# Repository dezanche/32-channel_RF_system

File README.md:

The 32-Channel RF Signal Amplifier and Attenuator System is a modular amplifier and attenuation system designed to provide 2nd stage amplification in close proximity to an MRI scanner. With proper choice of components it can readily be adapted to a wide range of Larmor frequencies and applications. Each channel’s amplifier and attenuator circuitry is housed on a separate daughterboard for flexibility and easy servicing.

These Daughterboards stand perpendicular to a larger Motherboard which contains all the common circuitry such as power distribution and protection circuitry, as well as the interface for attenuation control.

Additional information is provided in [this YouTube video](https://www.youtube.com/watch?v=jpFOpedchC8).

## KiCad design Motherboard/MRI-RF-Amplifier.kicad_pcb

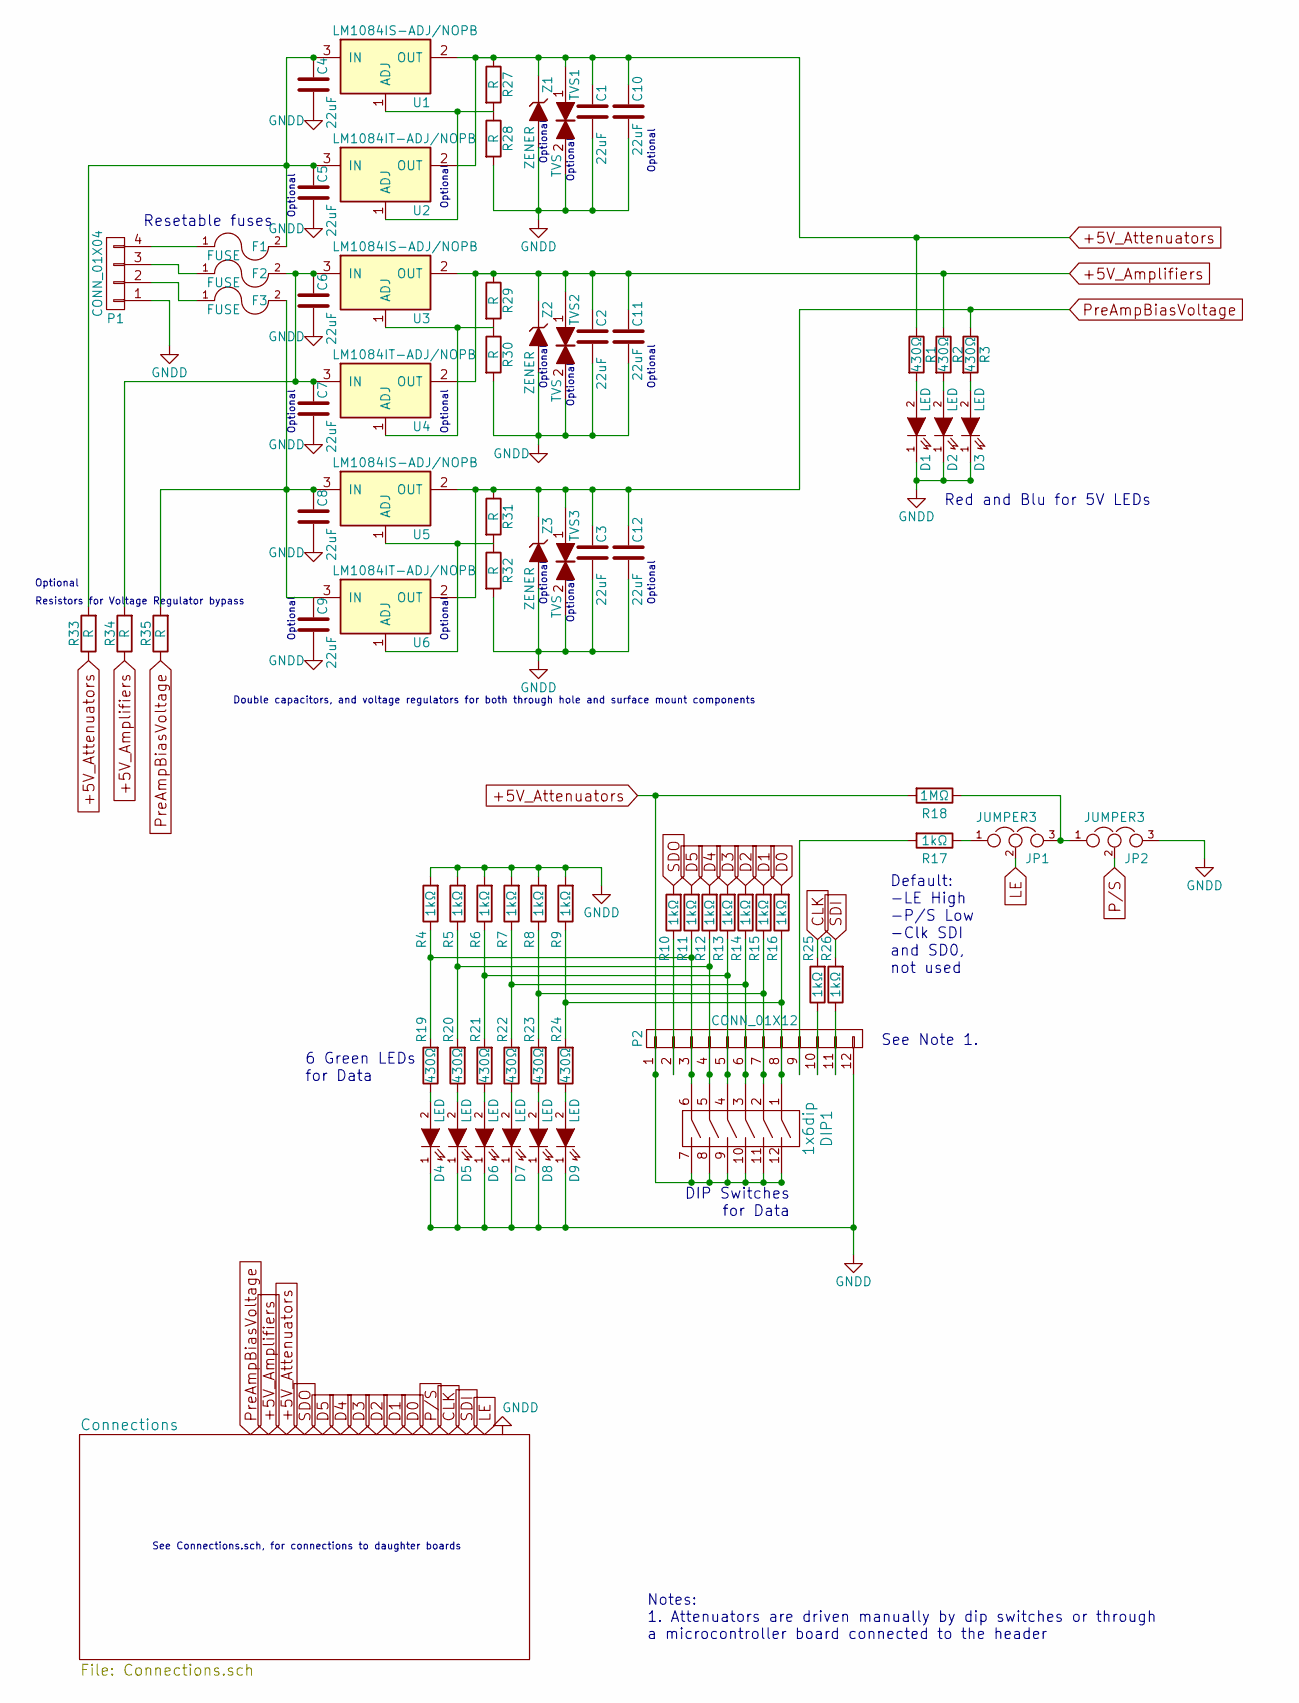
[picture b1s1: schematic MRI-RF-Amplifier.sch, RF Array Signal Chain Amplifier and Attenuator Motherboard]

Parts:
C1, C2, C3, C4, C6, C8: 22uF; C_1206_HandSoldering
C5, C7, C9, C10, C11, C12: 22uF; CP_Radial_D5.0mm_P2.00mm
D1, D2, D3, D4, D5, D6, D7, D8, D9: LED; LED_1206
DIP1: 1x6dip; DIP_SPSTx6
F1, F2, F3: FUSE; C_1210_HandSoldering
JP1, JP2: JUMPER3; Molex_KK-6410-03_03x2.54mm_Straight
P1: CONN_01X04; OSTTC0421162
P2: CONN_01X12; Pin_Header_Straight_1x12_Pitch2.54mm
R1, R2, R3, R19, R20, R21, R22, R23, R24: 430Ω; R_1206_HandSoldering
R4, R5, R6, R7, R8, R9, R10, R11, R12, R13, R14, R15, R16, R17, R25, R26: 1kΩ; R_1206_HandSoldering
R18: 1MΩ; R_1206_HandSoldering
R27, R28, R29, R30, R31, R32, R33, R34, R35: R; R_1206_HandSoldering
TVS1, TVS2, TVS3: TVS; D_SOD-323_HandSoldering
U1, U3, U5: LM1084IS-ADJ/NOPB; TO-263-3_TabPin2
U2, U4, U6: LM1084IT-ADJ/NOPB; TO-220_Horizontal
Z1, Z2, Z3: ZENER; D_SMB_Handsoldering

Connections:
+5V_Amplifiers: C2.1, C11.1, R2.1, R29.1, R34.1, TVS2.1, U3.2 (OUT), U4.2 (OUT), Z2.1 (K); also elsewhere on the board
+5V_Attenuators: C1.1, C10.1, DIP1.7, DIP1.8, DIP1.9, DIP1.10, DIP1.11, DIP1.12, P2.1, R1.1, R18.2, R27.1, R33.1, TVS1.1, U1.2 (OUT), U2.2 (OUT), Z1.1 (K); also elsewhere on the board
CLK: R25.2; also elsewhere on the board
D0: R16.2; also elsewhere on the board
D1: R15.2; also elsewhere on the board
D2: R14.2; also elsewhere on the board
D3: R13.2; also elsewhere on the board
D4: R12.2; also elsewhere on the board
D5: R11.2; also elsewhere on the board
GNDD: C1.2, C2.2, C3.2, C4.2, C5.2, C6.2, C7.2, C8.2, C9.2, C10.2, C11.2, C12.2, D1.1 (K), D2.1 (K), D3.1 (K), D4.1 (K), D5.1 (K), D6.1 (K), D7.1 (K), D8.1 (K), D9.1 (K), JP2.3, P1.1, P2.12, R4.2, R5.2, R6.2, R7.2, R8.2, R9.2, R28.2, R30.2, R32.2, TVS1.2, TVS2.2, TVS3.2, Z1.2 (A), Z2.2 (A), Z3.2 (A); also elsewhere on the board
LE: JP1.2; also elsewhere on the board
unnamed: C4.1, C5.1, F1.2, R33.2, U1.3 (IN), U2.3 (IN)
unnamed: C6.1, C7.1, F2.2, R34.2, U3.3 (IN), U4.3 (IN)
unnamed: C8.1, C9.1, F3.2, R35.2, U5.3 (IN), U6.3 (IN)
unnamed: D1.2 (A), R1.2
unnamed: D2.2 (A), R2.2
unnamed: D3.2 (A), R3.2
unnamed: D4.2 (A), R19.1
unnamed: D5.2 (A), R20.1
unnamed: D6.2 (A), R21.1
unnamed: D7.2 (A), R22.1
unnamed: D8.2 (A), R23.1
unnamed: D9.2 (A), R24.1
unnamed: DIP1.1, P2.8, R9.1, R16.1, R24.2
unnamed: DIP1.2, P2.7, R8.1, R15.1, R23.2
unnamed: DIP1.3, P2.6, R7.1, R14.1, R22.2
unnamed: DIP1.4, P2.5, R6.1, R13.1, R21.2
unnamed: DIP1.5, P2.4, R5.1, R12.1, R20.2
unnamed: DIP1.6, P2.3, R4.1, R11.1, R19.2
unnamed: F1.1, P1.4
unnamed: F2.1, P1.3
unnamed: F3.1, P1.2
unnamed: JP1.1, R17.1
unnamed: JP1.3, JP2.1, R18.1
unnamed: P2.2, R10.1
unnamed: P2.9, R17.2
unnamed: P2.10, R25.1
unnamed: P2.11, R26.1
unnamed: R27.2, R28.1, U1.1 (ADJ), U2.1 (ADJ)
unnamed: R29.2, R30.1, U3.1 (ADJ), U4.1 (ADJ)
unnamed: R31.2, R32.1, U5.1 (ADJ), U6.1 (ADJ)
P/S: JP2.2; also elsewhere on the board
PreAmpBiasVoltage: C3.1, C12.1, R3.1, R31.1, R35.1, TVS3.1, U5.2 (OUT), U6.2 (OUT), Z3.1 (K); also elsewhere on the board
SDI: R26.2; also elsewhere on the board
SDO: R10.2; also elsewhere on the board

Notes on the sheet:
Notes: 1. Attenuators are driven manually by dip switches or through a microcontroller board connected to the header
6 Green LEDs for Data
DIP Switches for Data
Default: -LE High -P/S Low -Clk SDI and SD0, not used
Resetable fuses
See Note 1.
Red and Blu for 5V LEDs
See Connections.sch, for connections to daughter boards
Double capacitors, and voltage regulators for both through hole and surface mount components
Resistors for Voltage Regulator bypass
Optional

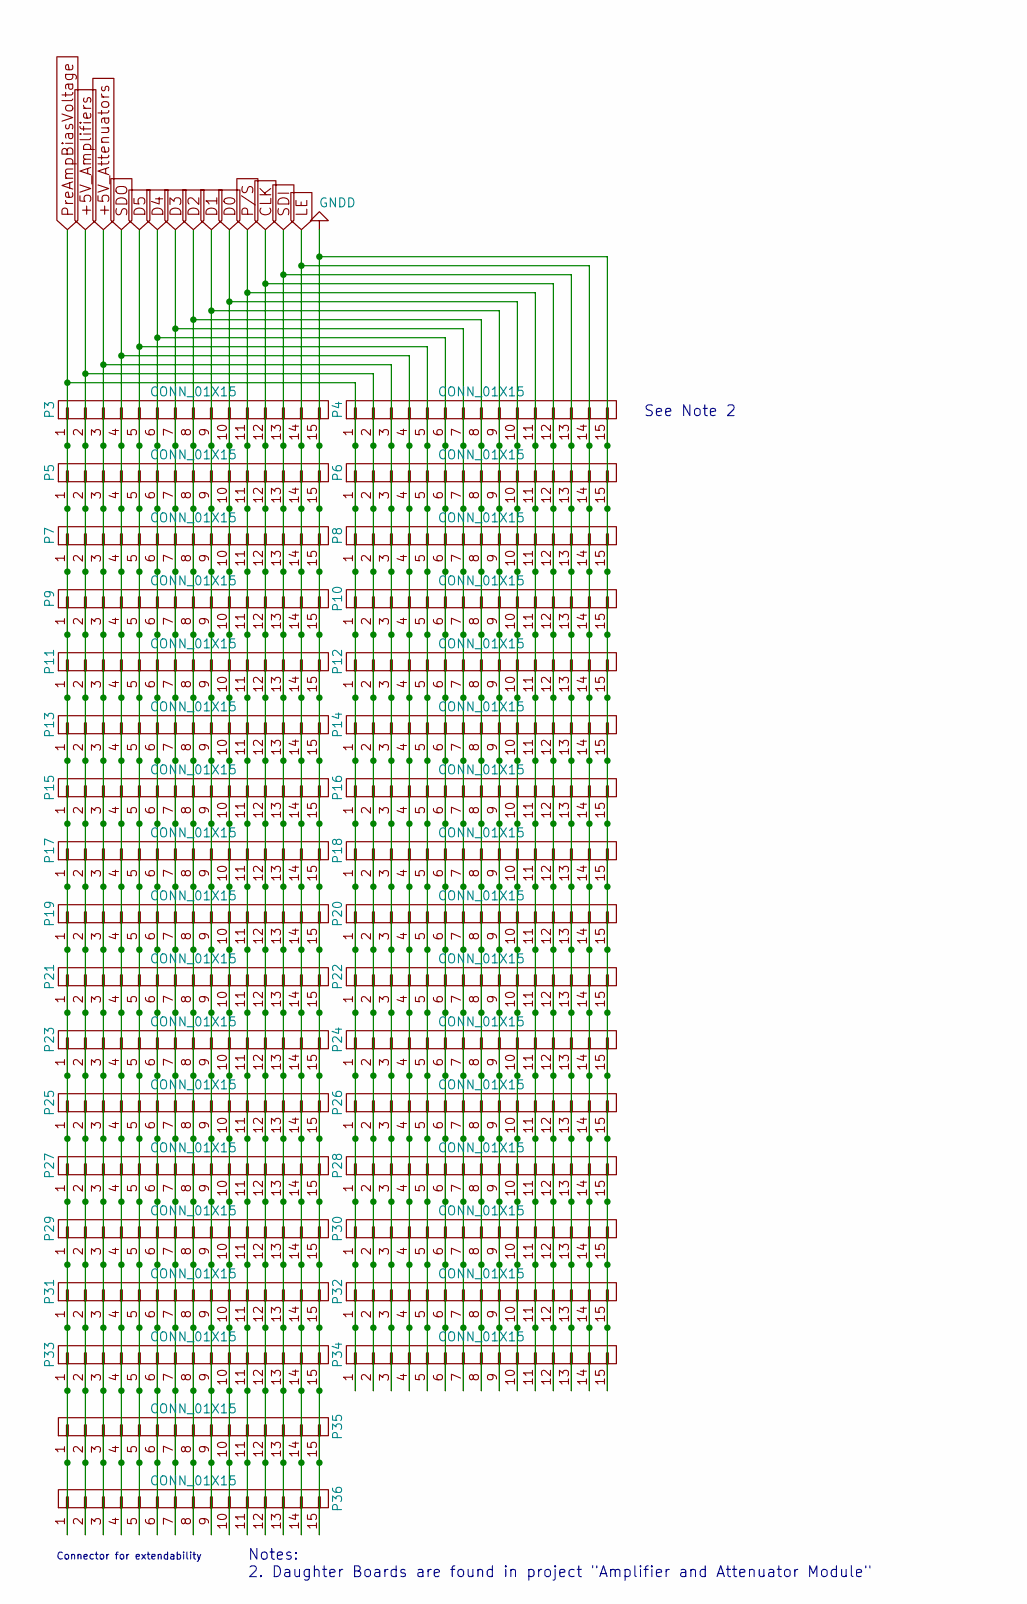
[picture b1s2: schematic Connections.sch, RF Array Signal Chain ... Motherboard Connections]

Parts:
P3, P4, P5, P6, P7, P8, P9, P10, P11, P12, P13, P14, P15, P16, P17, P18, P19, P20, P21, P22, P23, P24, P25, P26, P27, P28, P29, P30, P31, P32, P33, P34: CONN_01X15; Pin_Header_Straight_1x15_Pitch2.54mm
P35, P36: CONN_01X15; Molex_kk4455_Edge_01x15

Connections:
+5V_Amplifiers: P3.2, P4.2, P5.2, P6.2, P7.2, P8.2, P9.2, P10.2, P11.2, P12.2, P13.2, P14.2, P15.2, P16.2, P17.2, P18.2, P19.2, P20.2, P21.2, P22.2, P23.2, P24.2, P25.2, P26.2, P27.2, P28.2, P29.2, P30.2, P31.2, P32.2, P33.2, P34.2, P35.2, P36.2; also elsewhere on the board
+5V_Attenuators: P3.3, P4.3, P5.3, P6.3, P7.3, P8.3, P9.3, P10.3, P11.3, P12.3, P13.3, P14.3, P15.3, P16.3, P17.3, P18.3, P19.3, P20.3, P21.3, P22.3, P23.3, P24.3, P25.3, P26.3, P27.3, P28.3, P29.3, P30.3, P31.3, P32.3, P33.3, P34.3, P35.3, P36.3; also elsewhere on the board
CLK: P3.12, P4.12, P5.12, P6.12, P7.12, P8.12, P9.12, P10.12, P11.12, P12.12, P13.12, P14.12, P15.12, P16.12, P17.12, P18.12, P19.12, P20.12, P21.12, P22.12, P23.12, P24.12, P25.12, P26.12, P27.12, P28.12, P29.12, P30.12, P31.12, P32.12, P33.12, P34.12, P35.12, P36.12; also elsewhere on the board
D0: P3.10, P4.10, P5.10, P6.10, P7.10, P8.10, P9.10, P10.10, P11.10, P12.10, P13.10, P14.10, P15.10, P16.10, P17.10, P18.10, P19.10, P20.10, P21.10, P22.10, P23.10, P24.10, P25.10, P26.10, P27.10, P28.10, P29.10, P30.10, P31.10, P32.10, P33.10, P34.10, P35.10, P36.10; also elsewhere on the board
D1: P3.9, P4.9, P5.9, P6.9, P7.9, P8.9, P9.9, P10.9, P11.9, P12.9, P13.9, P14.9, P15.9, P16.9, P17.9, P18.9, P19.9, P20.9, P21.9, P22.9, P23.9, P24.9, P25.9, P26.9, P27.9, P28.9, P29.9, P30.9, P31.9, P32.9, P33.9, P34.9, P35.9, P36.9; also elsewhere on the board
D2: P3.8, P4.8, P5.8, P6.8, P7.8, P8.8, P9.8, P10.8, P11.8, P12.8, P13.8, P14.8, P15.8, P16.8, P17.8, P18.8, P19.8, P20.8, P21.8, P22.8, P23.8, P24.8, P25.8, P26.8, P27.8, P28.8, P29.8, P30.8, P31.8, P32.8, P33.8, P34.8, P35.8, P36.8; also elsewhere on the board
D3: P3.7, P4.7, P5.7, P6.7, P7.7, P8.7, P9.7, P10.7, P11.7, P12.7, P13.7, P14.7, P15.7, P16.7, P17.7, P18.7, P19.7, P20.7, P21.7, P22.7, P23.7, P24.7, P25.7, P26.7, P27.7, P28.7, P29.7, P30.7, P31.7, P32.7, P33.7, P34.7, P35.7, P36.7; also elsewhere on the board
D4: P3.6, P4.6, P5.6, P6.6, P7.6, P8.6, P9.6, P10.6, P11.6, P12.6, P13.6, P14.6, P15.6, P16.6, P17.6, P18.6, P19.6, P20.6, P21.6, P22.6, P23.6, P24.6, P25.6, P26.6, P27.6, P28.6, P29.6, P30.6, P31.6, P32.6, P33.6, P34.6, P35.6, P36.6; also elsewhere on the board
D5: P3.5, P4.5, P5.5, P6.5, P7.5, P8.5, P9.5, P10.5, P11.5, P12.5, P13.5, P14.5, P15.5, P16.5, P17.5, P18.5, P19.5, P20.5, P21.5, P22.5, P23.5, P24.5, P25.5, P26.5, P27.5, P28.5, P29.5, P30.5, P31.5, P32.5, P33.5, P34.5, P35.5, P36.5; also elsewhere on the board
GNDD: P3.15, P4.15, P5.15, P6.15, P7.15, P8.15, P9.15, P10.15, P11.15, P12.15, P13.15, P14.15, P15.15, P16.15, P17.15, P18.15, P19.15, P20.15, P21.15, P22.15, P23.15, P24.15, P25.15, P26.15, P27.15, P28.15, P29.15, P30.15, P31.15, P32.15, P33.15, P34.15, P35.15, P36.15; also elsewhere on the board
LE: P3.14, P4.14, P5.14, P6.14, P7.14, P8.14, P9.14, P10.14, P11.14, P12.14, P13.14, P14.14, P15.14, P16.14, P17.14, P18.14, P19.14, P20.14, P21.14, P22.14, P23.14, P24.14, P25.14, P26.14, P27.14, P28.14, P29.14, P30.14, P31.14, P32.14, P33.14, P34.14, P35.14, P36.14; also elsewhere on the board
P/S: P3.11, P4.11, P5.11, P6.11, P7.11, P8.11, P9.11, P10.11, P11.11, P12.11, P13.11, P14.11, P15.11, P16.11, P17.11, P18.11, P19.11, P20.11, P21.11, P22.11, P23.11, P24.11, P25.11, P26.11, P27.11, P28.11, P29.11, P30.11, P31.11, P32.11, P33.11, P34.11, P35.11, P36.11; also elsewhere on the board
PreAmpBiasVoltage: P3.1, P4.1, P5.1, P6.1, P7.1, P8.1, P9.1, P10.1, P11.1, P12.1, P13.1, P14.1, P15.1, P16.1, P17.1, P18.1, P19.1, P20.1, P21.1, P22.1, P23.1, P24.1, P25.1, P26.1, P27.1, P28.1, P29.1, P30.1, P31.1, P32.1, P33.1, P34.1, P35.1, P36.1; also elsewhere on the board
SDI: P3.13, P4.13, P5.13, P6.13, P7.13, P8.13, P9.13, P10.13, P11.13, P12.13, P13.13, P14.13, P15.13, P16.13, P17.13, P18.13, P19.13, P20.13, P21.13, P22.13, P23.13, P24.13, P25.13, P26.13, P27.13, P28.13, P29.13, P30.13, P31.13, P32.13, P33.13, P34.13, P35.13, P36.13; also elsewhere on the board
SDO: P3.4, P4.4, P5.4, P6.4, P7.4, P8.4, P9.4, P10.4, P11.4, P12.4, P13.4, P14.4, P15.4, P16.4, P17.4, P18.4, P19.4, P20.4, P21.4, P22.4, P23.4, P24.4, P25.4, P26.4, P27.4, P28.4, P29.4, P30.4, P31.4, P32.4, P33.4, P34.4, P35.4, P36.4; also elsewhere on the board

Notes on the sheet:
Connector for extendability
Notes: 2. Daughter Boards are found in project "Amplifier and Attenuator Module"
See Note 2

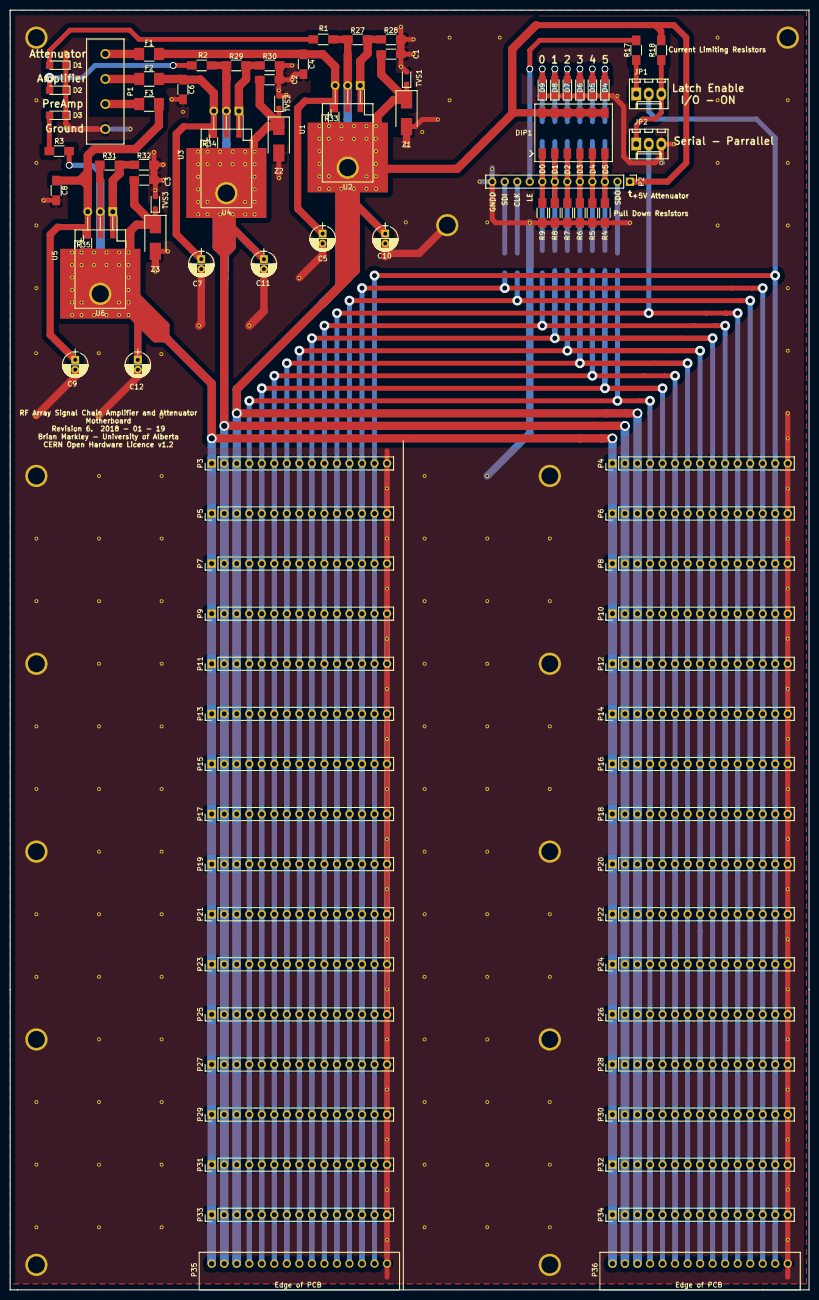
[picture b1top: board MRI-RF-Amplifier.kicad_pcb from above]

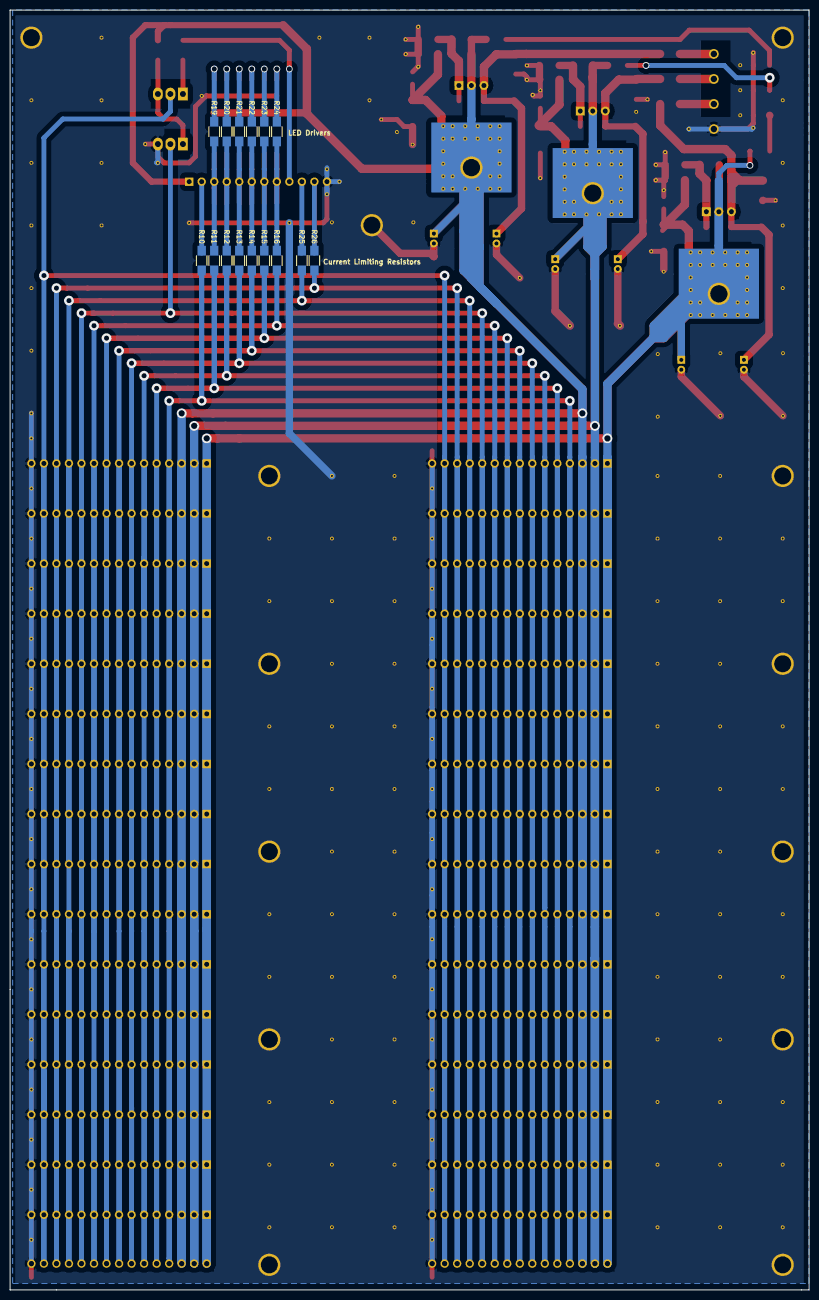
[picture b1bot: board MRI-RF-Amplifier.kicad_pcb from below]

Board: 2 copper layers, 162.1 x 259.6 mm, 110 parts (15 on the bottom side), 45 nets.

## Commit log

2018-07-21 Daughterboard Files
2018-07-21 Motherboard Files
2018-07-21 Parts Lists and Component Datasheets
2018-07-21 Photos
2018-07-21 Test Results

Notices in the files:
Motherboard/Connections.sch:
CERN Open Hardware Licence v1.2
